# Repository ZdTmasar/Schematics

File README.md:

# Schematics
Some of my schematics circuit

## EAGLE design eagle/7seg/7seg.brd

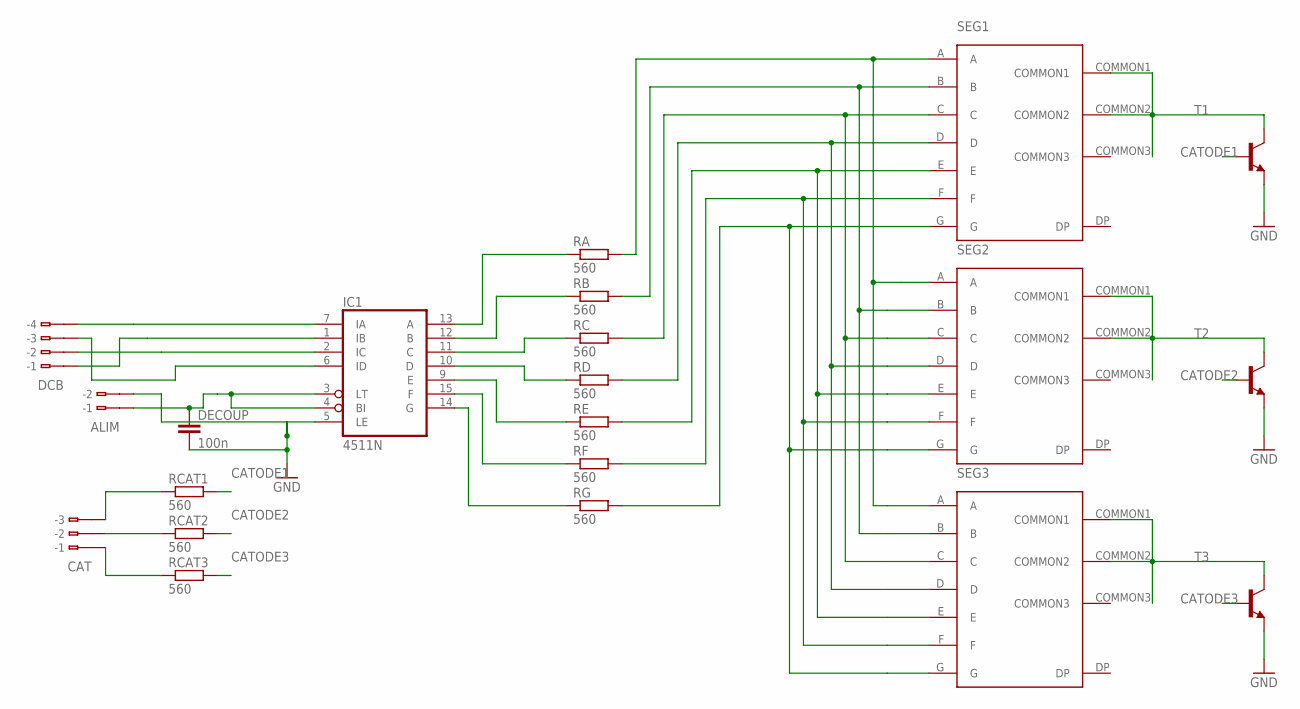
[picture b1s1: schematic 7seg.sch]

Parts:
ALIM: 233-102
CAT: 233-103
DCB: 233-104
DECOUP: 100n; C2012
IC1: 4511N; DIL16
RA: 560; M2012
RB: 560; M2012
RC: 560; M2012
RCAT1, RCAT2, RCAT3: 560; M2012
RD: 560; M2012
RE: 560; M2012
RF: 560; M2012
RG: 560; M2012
SEG1, SEG2, SEG3: 7SEG_33MMMARK1; 7SEG_33MM
T1, T2, T3: BF844-NPN-TO92-CBE; TO92-CBE

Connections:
CATODE1: RCAT1.2, T1.B
CATODE2: RCAT2.2, T2.B
CATODE3: RCAT3.2, T3.B
DCB: DCB.B1 (B-1), IC1.1 (IB)
GND: ALIM.B2 (B-2), DECOUP.2, IC1.5 (LE), T1.E, T2.E, T3.E
unnamed: RA.2, SEG1.A, SEG2.A, SEG3.A
unnamed: RB.2, SEG1.B, SEG2.B, SEG3.B
unnamed: RC.2, SEG1.C, SEG2.C, SEG3.C
unnamed: RD.2, SEG1.D, SEG2.D, SEG3.D
unnamed: RE.2, SEG1.E, SEG2.E, SEG3.E
unnamed: RF.2, SEG1.F, SEG2.F, SEG3.F
unnamed: RG.2, SEG1.G, SEG2.G, SEG3.G
unnamed: IC1.13 (A), RA.1
unnamed: IC1.12 (B), RB.1
unnamed: IC1.11 (C), RC.1
unnamed: IC1.10 (D), RD.1
unnamed: IC1.9 (E), RE.1
unnamed: IC1.15 (F), RF.1
unnamed: IC1.14 (G), RG.1
unnamed: SEG1.COMMON1, SEG1.COMMON2, T1.C
unnamed: SEG2.COMMON1, SEG2.COMMON2, T2.C
unnamed: SEG3.COMMON1, SEG3.COMMON2, T3.C
unnamed: DCB.B4 (B-4), IC1.7 (IA)
unnamed: DCB.B2 (B-2), IC1.2 (IC)
unnamed: DCB.B3 (B-3), IC1.6 (ID)
unnamed: ALIM.B1 (B-1), DECOUP.1, IC1.3 (LT), IC1.4 (BI)
unnamed: CAT.B3 (B-3), RCAT1.1
unnamed: CAT.B2 (B-2), RCAT2.1
unnamed: CAT.B1 (B-1), RCAT3.1
VDD: IC1.16 (VDD)
VSS: IC1.8 (VSS)

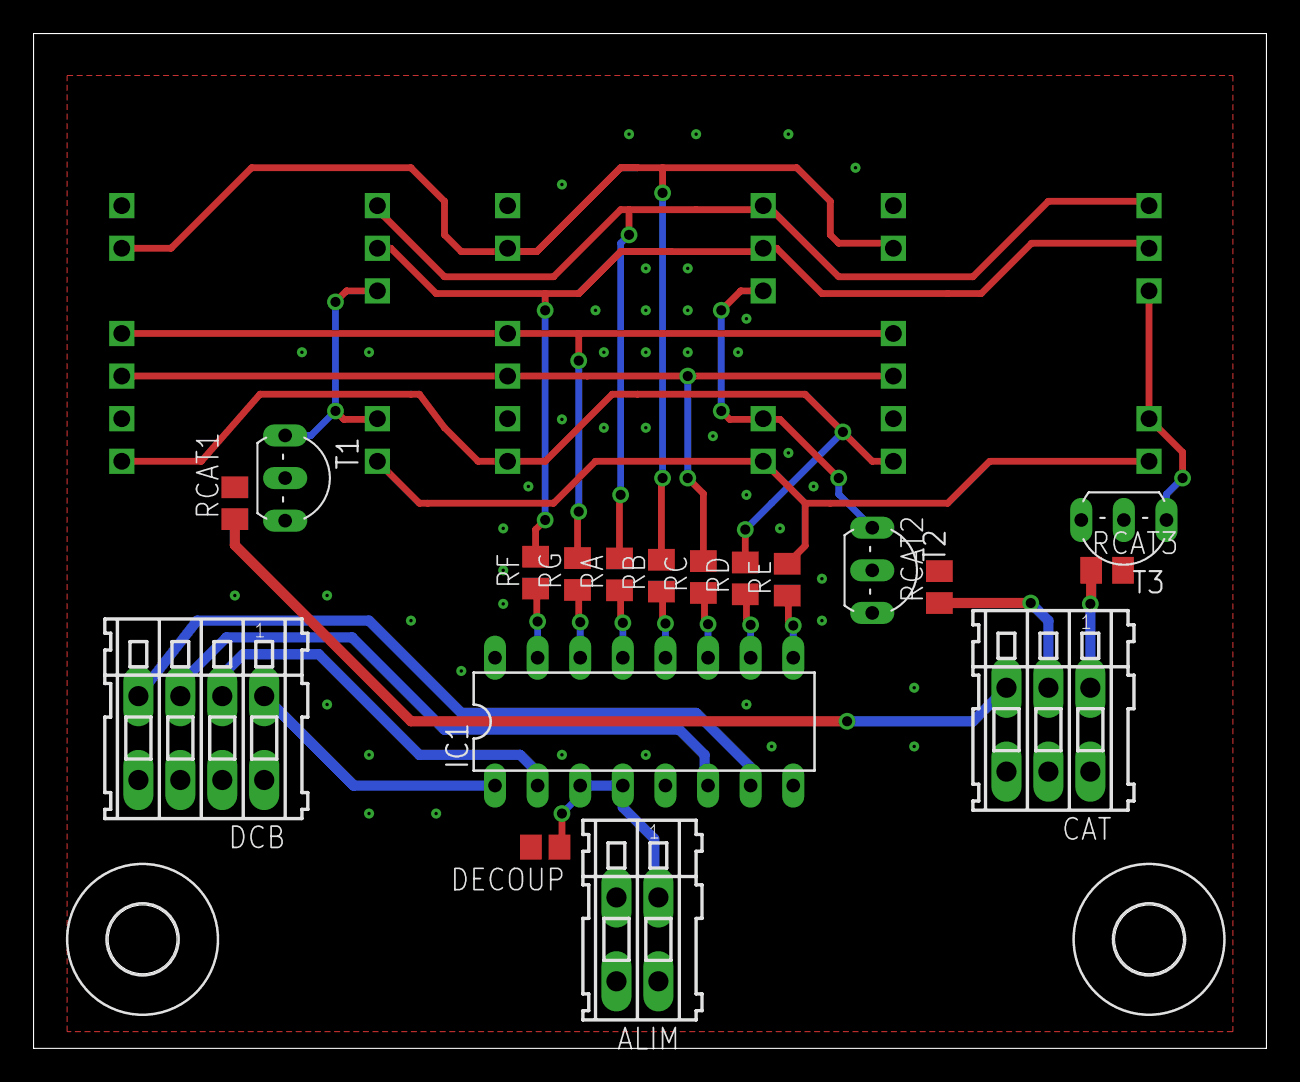
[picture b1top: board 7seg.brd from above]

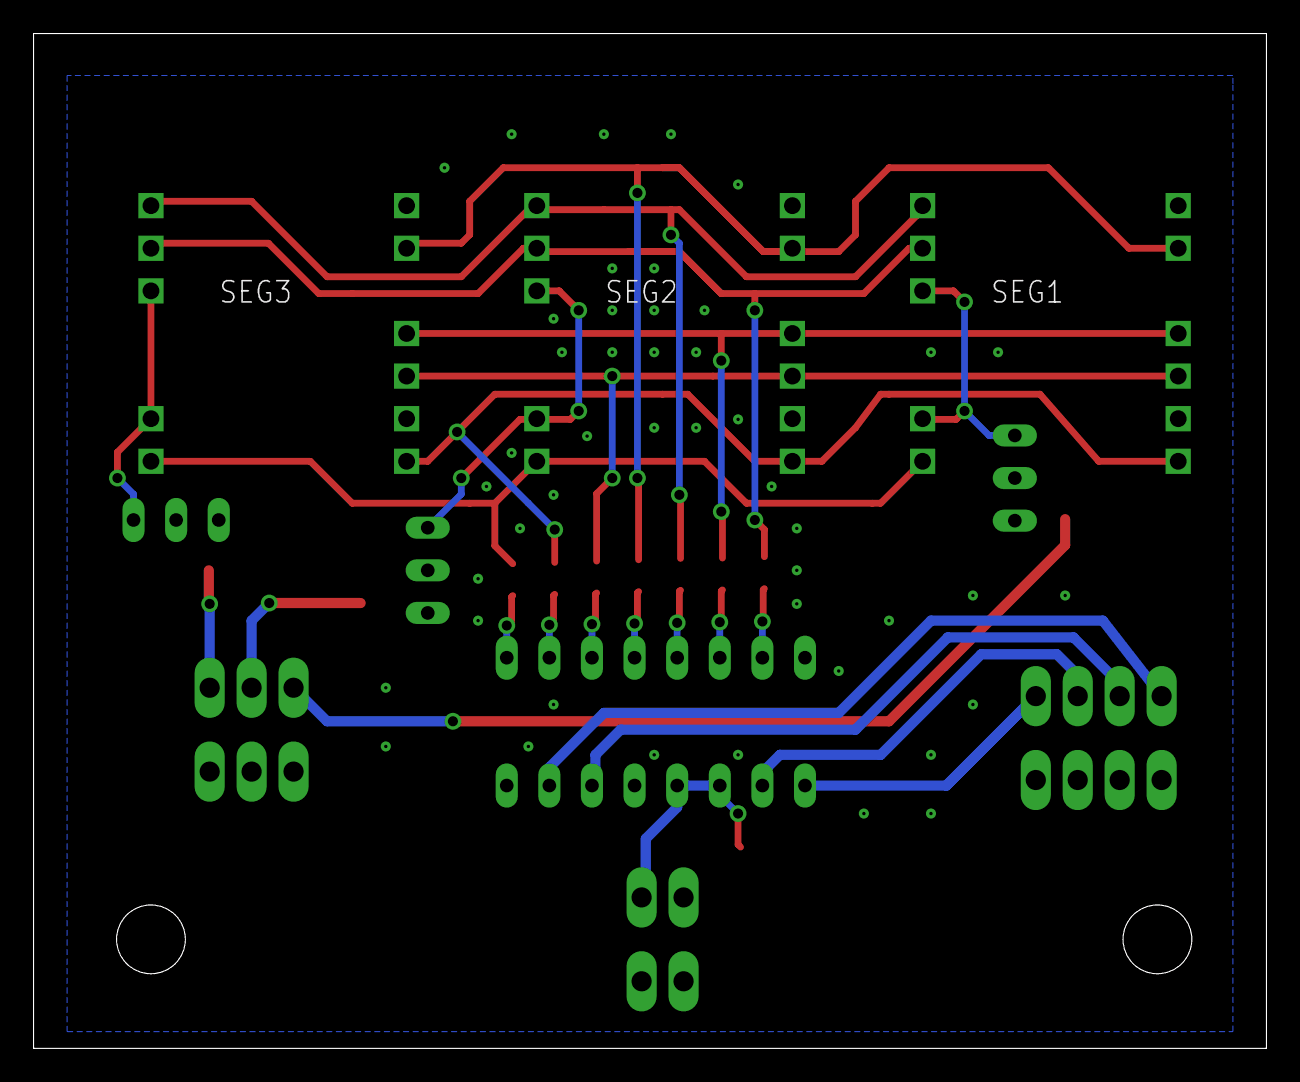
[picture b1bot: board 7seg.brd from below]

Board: 2 copper layers, 73.5 x 60.5 mm, 23 parts (3 on the bottom side), 29 nets.

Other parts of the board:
U$1, U$2: 4,1

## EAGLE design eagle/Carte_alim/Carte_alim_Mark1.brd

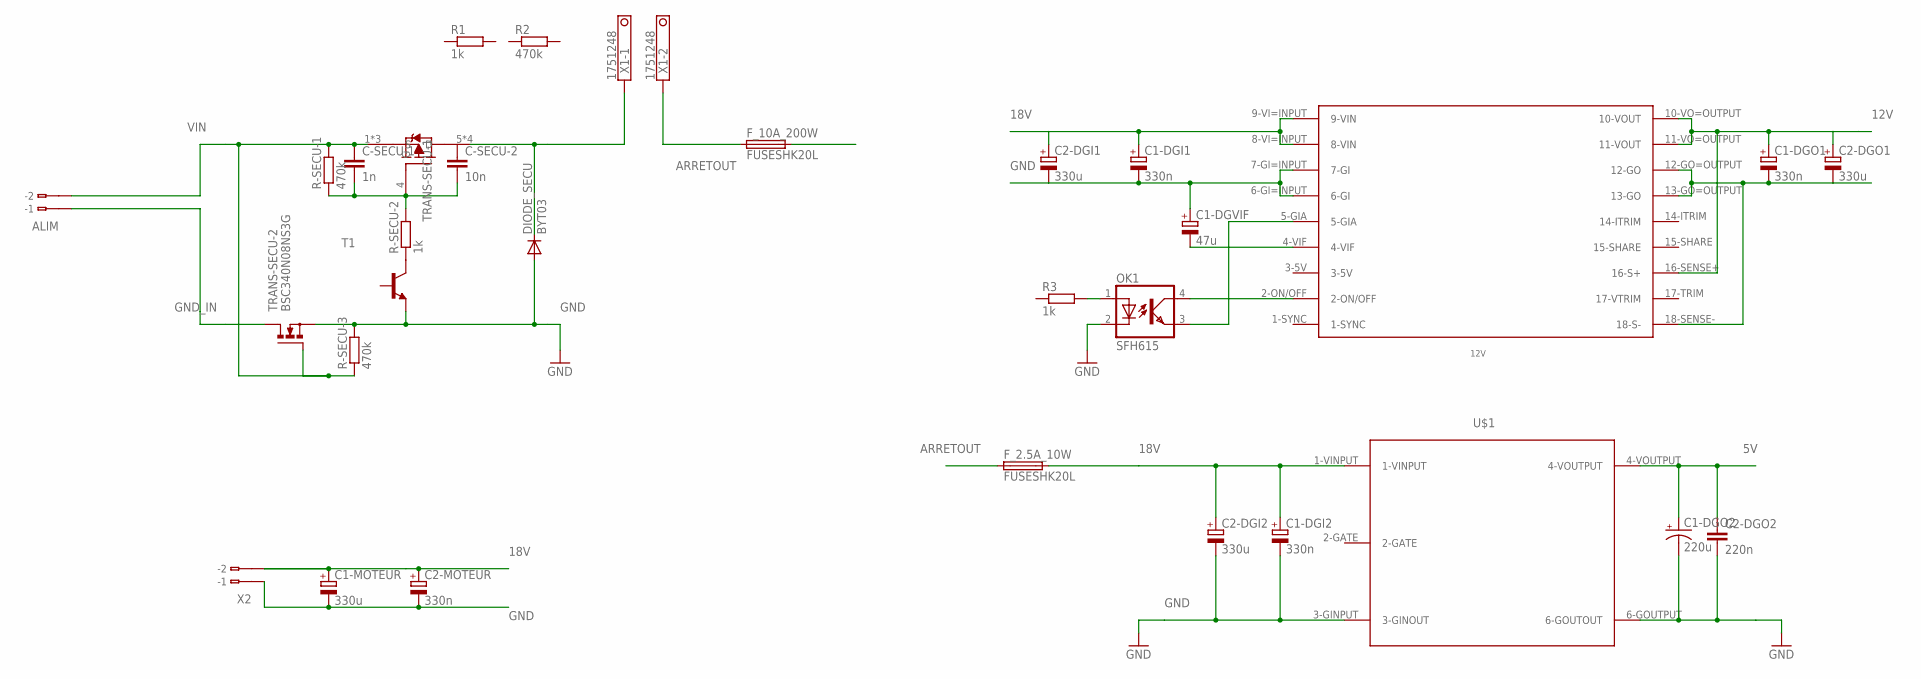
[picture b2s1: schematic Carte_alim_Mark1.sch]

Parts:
12V: MGDS200MGDS200; MGDS200
ALIM: 233-102; MPN 233-102
C1-DGI1, C1-DGI2, C1-DGO1, C2-MOTEUR: 330n; E2-5
C1-DGO2: 220u; 085CS_1AW
C1-DGVIF: 47u; E2-5
C1-MOTEUR, C2-DGI1, C2-DGI2, C2-DGO1: 330u; E3,5-10
C2-DGO2: 220n; C2012
C-SECU-1: 1n; C025-024X044
C-SECU-2: 10n; C075-032X103
DIODE_SECU: BYT03; DO27-15
F_2.5A_10W, F_10A_200W: FUSESHK20L; SHK20L
OK1: SFH615; DIL04
R1, R3: 1k; R2012
R2: 470k; R2012
R-SECU-1, R-SECU-3: 470k; 0207/7
R-SECU-2: 1k; 0207/7
T1: BF844-NPN-TO92-CBE; TO92-CBE
TRANS-SECU-1: BSC080PG-TDSON; PG-TDSON-8
TRANS-SECU-2: BSC340N08NS3G; PG-TDSON-8
U$1: MGDS10SINGLE; MGDS10
X1: 1751248
X2: 233-102

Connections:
5V: C1-DGO2.+, C2-DGO2.1, U$1.4-VOUTPUT
12V: 12V.10-VO=OUTPUT (10-VOUT), 12V.11-VO=OUTPUT (11-VOUT), 12V.16-SENSE+ (16-S+), C1-DGO1.+, C2-DGO1.+
18V: 12V.8-VI=INPUT (8-VIN), 12V.9-VI=INPUT (9-VIN), C1-DGI1.+, C1-DGI2.+, C1-MOTEUR.+, C2-DGI1.+, C2-DGI2.+, C2-MOTEUR.+, F_2.5A_10W.2A (2), F_10A_200W.2A (2), U$1.1-VINPUT, X2.B2 (B-2)
ARRETOUT: F_2.5A_10W.1A (1), F_10A_200W.1A (1), X1.2
GND: 12V.6-GI=INPUT (6-GI), 12V.7-GI=INPUT (7-GI), 12V.12-GO=OUTPUT (12-GO), 12V.13-GO=OUTPUT (13-GO), 12V.18-SENSE- (18-S-), C1-DGI1.-, C1-DGI2.-, C1-DGO1.-, C1-DGO2.-, C1-DGVIF.+, C1-MOTEUR.-, C2-DGI1.-, C2-DGI2.-, C2-DGO1.-, C2-DGO2.2, C2-MOTEUR.-, DIODE_SECU.A, OK1.2 (C), R-SECU-3.2, T1.E, TRANS-SECU-2.1 (S), TRANS-SECU-2.2 (S), TRANS-SECU-2.3 (S), U$1.3-GINPUT (3-GINOUT), U$1.6-GOUTPUT (6-GOUTOUT), X2.B1 (B-1)
GND_IN: ALIM.B1 (B-1), TRANS-SECU-2.5 (D), TRANS-SECU-2.6 (D), TRANS-SECU-2.7 (D), TRANS-SECU-2.8 (D)
unnamed: DIODE_SECU.C, TRANS-SECU-1.5 (D), TRANS-SECU-1.6 (D), TRANS-SECU-1.7 (D), TRANS-SECU-1.8 (D), X1.1
unnamed: OK1.1 (A), R3.2
unnamed: C-SECU-1.2, C-SECU-2.2, R-SECU-1.1, R-SECU-2.2, TRANS-SECU-1.4 (G)
unnamed: R-SECU-2.1, T1.C
unnamed: 12V.4-VIF, C1-DGVIF.-
unnamed: 12V.5-GIA, OK1.3 (EMIT)
unnamed: 12V.2-ON/OFF, OK1.4 (COL)
VIN: ALIM.B2 (B-2), C-SECU-1.1, R-SECU-1.2, R-SECU-3.1, TRANS-SECU-1.1 (S), TRANS-SECU-1.2 (S), TRANS-SECU-1.3 (S), TRANS-SECU-2.4 (G)

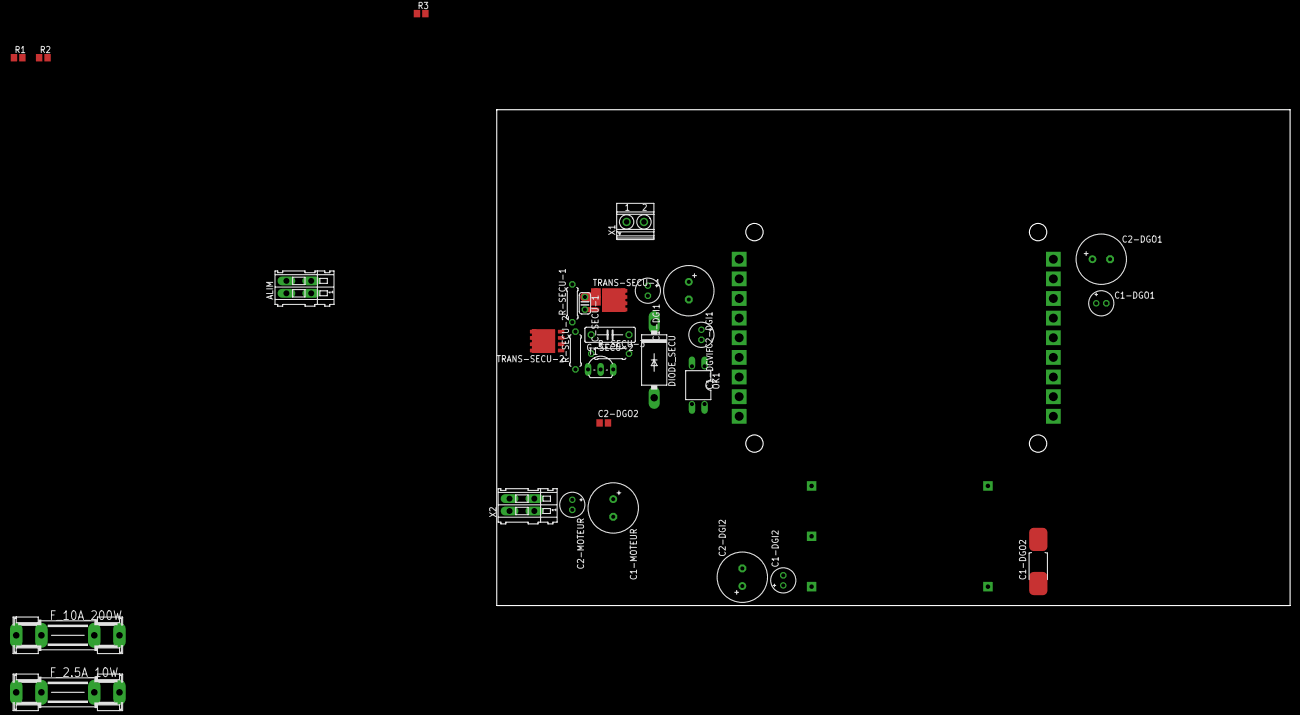
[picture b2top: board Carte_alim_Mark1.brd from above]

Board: 2 copper layers, 160.0 x 100.0 mm, 31 parts (0 on the bottom side), 14 nets.

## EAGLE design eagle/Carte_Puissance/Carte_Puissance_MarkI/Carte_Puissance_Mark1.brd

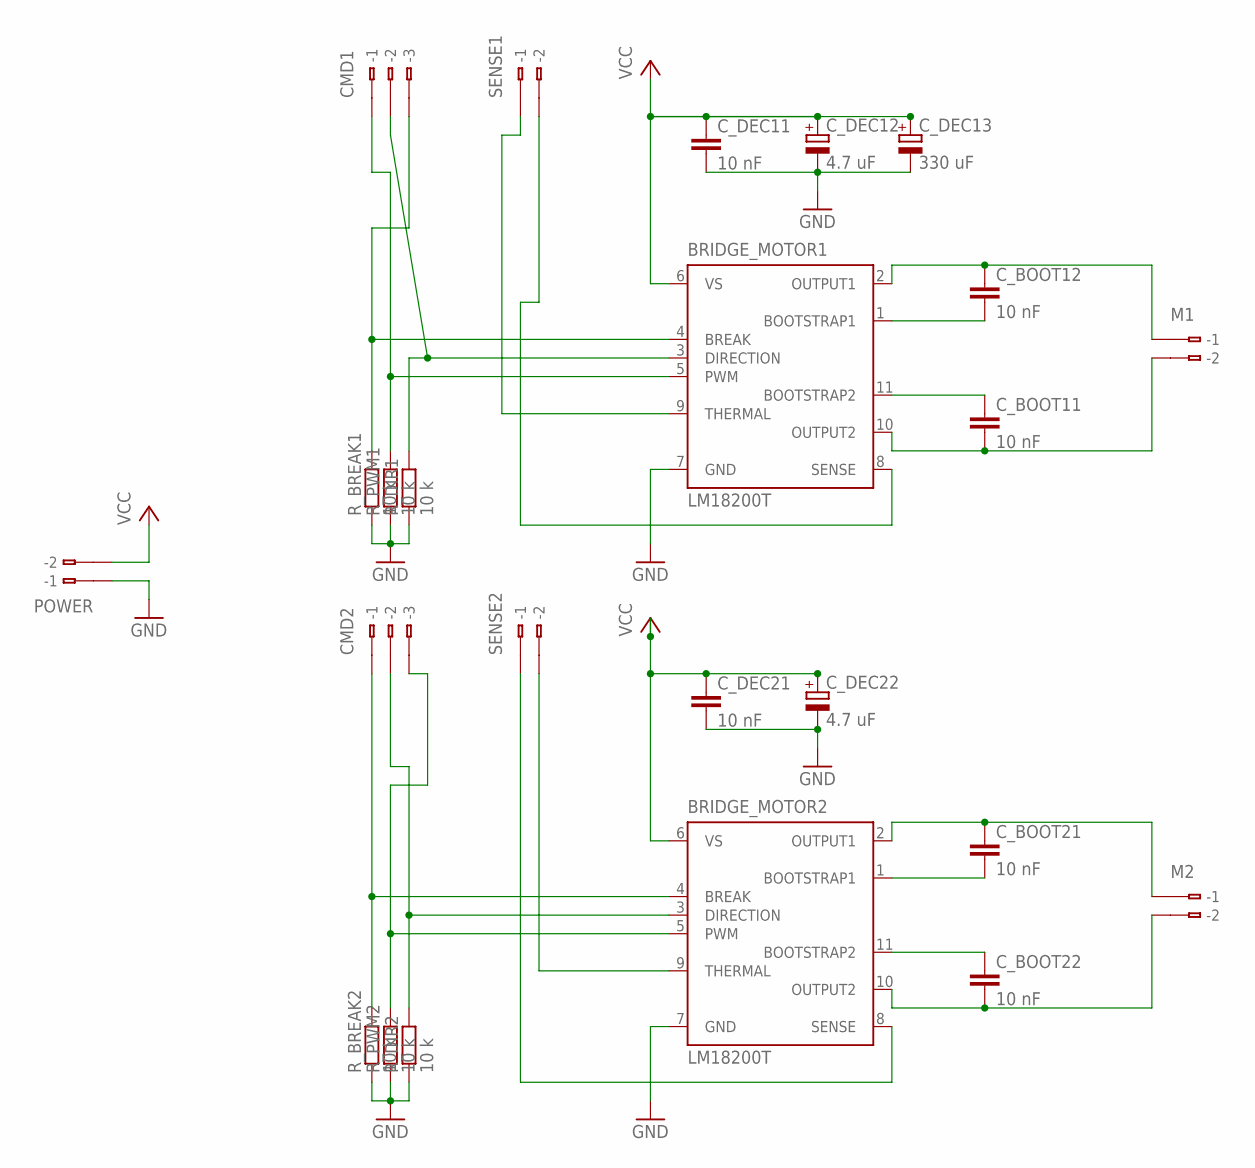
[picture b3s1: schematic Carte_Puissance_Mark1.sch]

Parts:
BRIDGE_MOTOR1, BRIDGE_MOTOR2: LM18200T; TO-220-11
CMD1, CMD2: 233-103; MPN 233-103
C_BOOT11, C_BOOT12, C_BOOT21, C_BOOT22: 10 nF; C5B3
C_DEC11, C_DEC21: 10 nF; C5B3
C_DEC12, C_DEC22: 4.7 uF; E2-5
C_DEC13: 330 uF; E5-10,5
M1, M2: 233-102
POWER: 233-102
R_BREAK1, R_BREAK2: 10 k; R2012
R_DIR1, R_DIR2: 10 k; R2012
R_PWM1, R_PWM2: 10 k; R2012
SENSE1, SENSE2: 233-102

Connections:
GND: BRIDGE_MOTOR1.7 (GND), BRIDGE_MOTOR2.7 (GND), C_DEC11.2, C_DEC12.-, C_DEC13.-, C_DEC21.2, C_DEC22.-, R_BREAK1.1, R_BREAK2.1, R_DIR1.1, R_DIR2.1, R_PWM1.1, R_PWM2.1
unnamed: BRIDGE_MOTOR1.4 (BREAK), CMD1.B3 (B-3), R_BREAK1.2
unnamed: BRIDGE_MOTOR1.5 (PWM), CMD1.B1 (B-1), R_PWM1.2
unnamed: BRIDGE_MOTOR2.11 (BOOTSTRAP2), C_BOOT22.1
unnamed: BRIDGE_MOTOR2.1 (BOOTSTRAP1), C_BOOT21.2
unnamed: BRIDGE_MOTOR2.2 (OUTPUT1), C_BOOT21.1, M2.B1 (B-1)
unnamed: BRIDGE_MOTOR2.10 (OUTPUT2), C_BOOT22.2, M2.B2 (B-2)
unnamed: BRIDGE_MOTOR1.11 (BOOTSTRAP2), C_BOOT11.1
unnamed: BRIDGE_MOTOR1.1 (BOOTSTRAP1), C_BOOT12.2
unnamed: BRIDGE_MOTOR1.2 (OUTPUT1), C_BOOT12.1, M1.B1 (B-1)
unnamed: BRIDGE_MOTOR1.10 (OUTPUT2), C_BOOT11.2, M1.B2 (B-2)
unnamed: BRIDGE_MOTOR1.3 (DIRECTION), CMD1.B2 (B-2), R_DIR1.2
unnamed: BRIDGE_MOTOR1.9 (THERMAL), SENSE1.B1 (B-1)
unnamed: BRIDGE_MOTOR1.8 (SENSE), SENSE1.B2 (B-2)
unnamed: BRIDGE_MOTOR2.4 (BREAK), CMD2.B1 (B-1), R_BREAK2.2
unnamed: BRIDGE_MOTOR2.5 (PWM), CMD2.B3 (B-3), R_PWM2.2
unnamed: BRIDGE_MOTOR2.3 (DIRECTION), CMD2.B2 (B-2), R_DIR2.2
unnamed: BRIDGE_MOTOR2.9 (THERMAL), SENSE2.B2 (B-2)
unnamed: BRIDGE_MOTOR2.8 (SENSE), SENSE2.B1 (B-1)
POWERT: POWER.B1 (B-1)
VCC: BRIDGE_MOTOR1.6 (VS), BRIDGE_MOTOR2.6 (VS), C_DEC11.1, C_DEC12.+, C_DEC13.+, C_DEC21.1, C_DEC22.+, POWER.B2 (B-2)

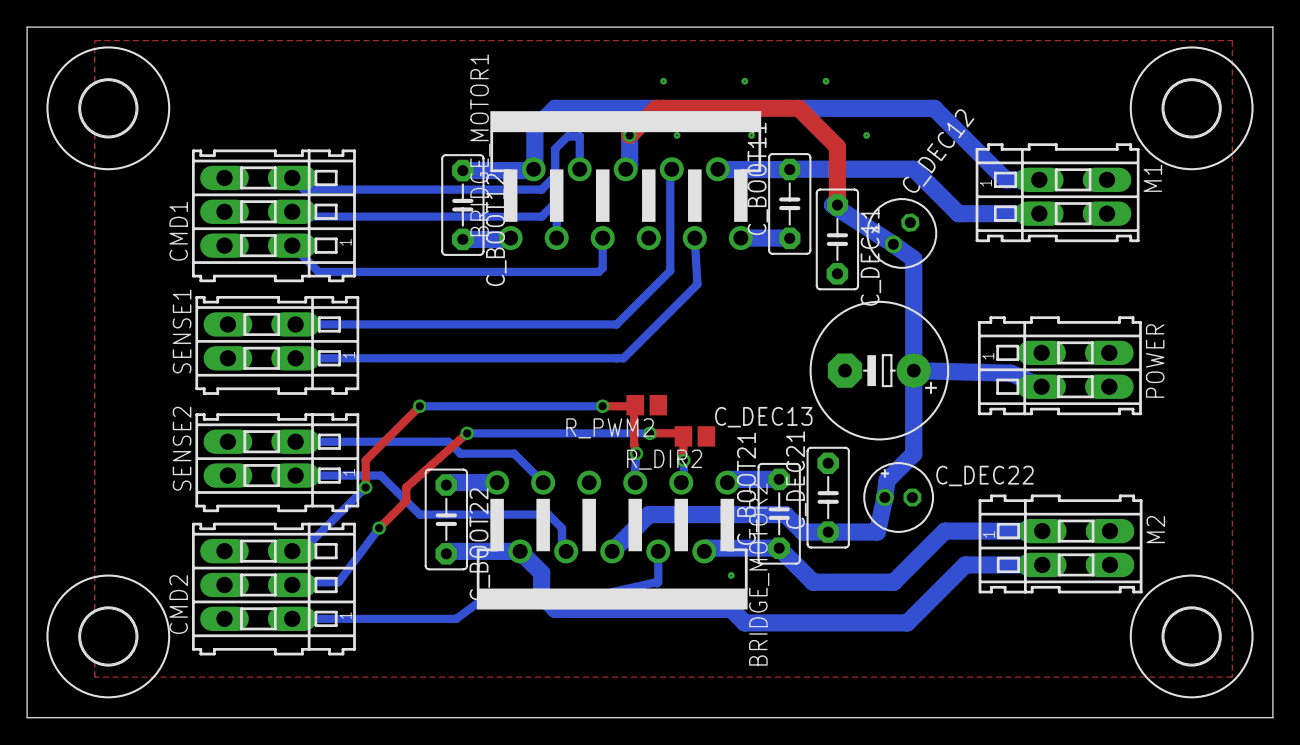
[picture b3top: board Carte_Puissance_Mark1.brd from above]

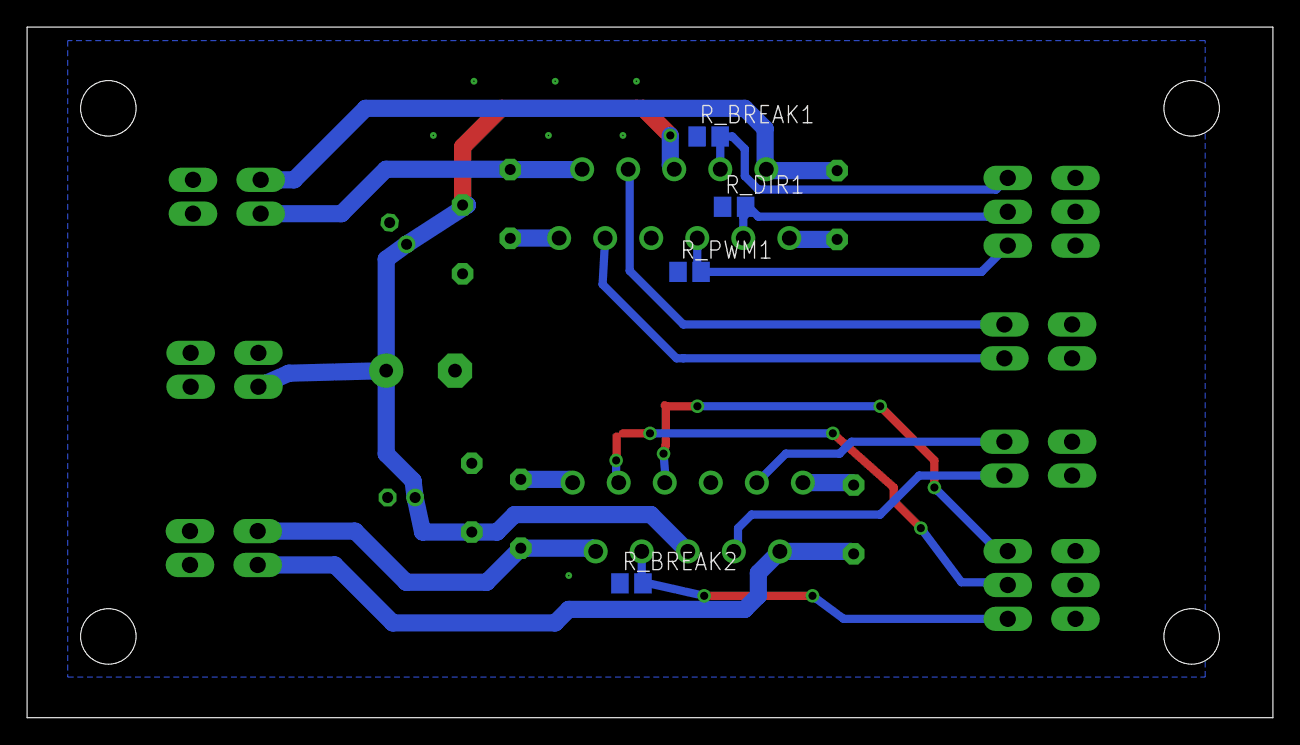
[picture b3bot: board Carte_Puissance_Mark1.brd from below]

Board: 2 copper layers, 92.0 x 51.0 mm, 28 parts (4 on the bottom side), 20 nets.

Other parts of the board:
U$1, U$2, U$3, U$4: 4,1
